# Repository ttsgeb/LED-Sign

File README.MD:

# LED Sign Board Revamp Project
This project aims to make the LED Sign Board a more valuable prototyping platform for learning usage of "neopixel" style LEDs  
It does this by developing the interface with the individual LED strips to enable easier wiring while also providing fusing for lengths of 64 LEDS  
Additionally it allows the 144/m strips to be spaced such that every two neopixels will make for one square pixel, which is satisfying despite halving the resolution when used.  

Parts list:
30m of 144/m WS2812 or compatible strip lights (~$400) 
2 * https://www.mcmaster.com/89015K189/  ~$100  
5/(2 Boards): https://www.digikey.com/en/products/detail/bourns-inc/MF-NSML400-12-2/9859205 ~$43 (60 total fuses)  
1/(2 Boards): https://www.digikey.com/en/products/detail/phoenix-contact/1017504/9346605 ~$12 (12 Connectors)  
Boards: https://www.pcbway.com/orderonline.aspx?outsideid=23cf7d91-80f4-4e14-90a0-6c2527d8c808 ~$55 (25 Boards)

Boards only total estimated cost: $110    Boards and backer total estimated cost: $210

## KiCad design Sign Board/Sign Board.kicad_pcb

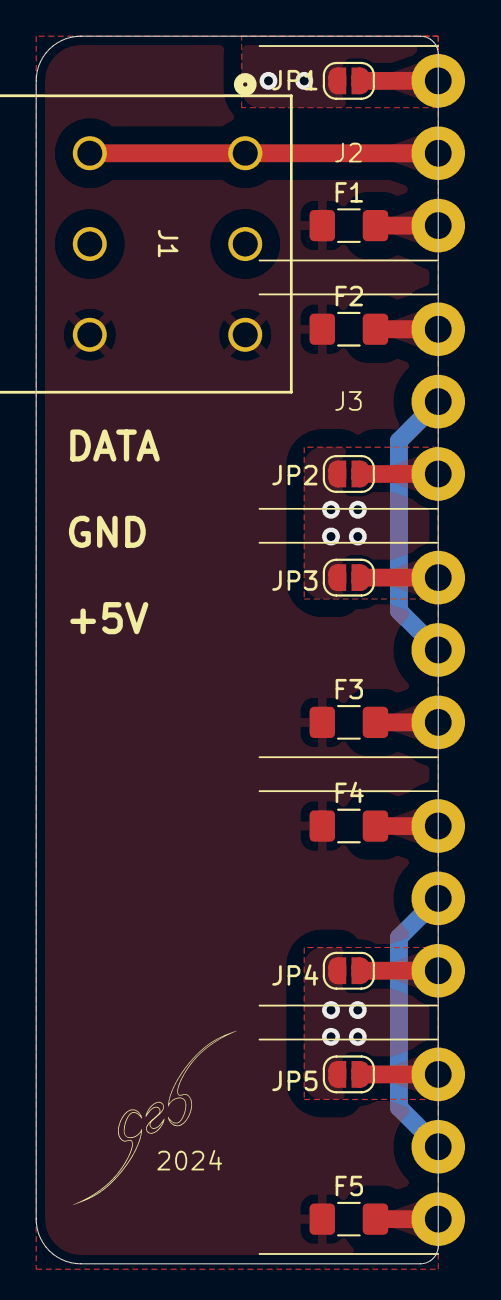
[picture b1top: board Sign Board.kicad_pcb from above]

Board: 2 copper layers, 22.5 x 68.7 mm, 17 parts (0 on the bottom side), 15 nets.

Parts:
2024: geblogo
F1, F2, F3, F4, F5: Polyfuse; Fuse_1206_3216Metric_Pad1.42x1.75mm_HandSolder
J1: Conn_01x03_Socket; CONN_1017492
J2, J3, J4, J5, J6: Conn_01x03_Pin; LED Strip Castlation
JP1, JP2, JP3, JP4, JP5: SolderJumper_2_Open; SolderJumper-2_P1.3mm_Open_RoundedPad1.0x1.5mm

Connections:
unnamed: F1.1, F2.1, F3.1, F4.1, F5.1, J1.5, J1.6
unnamed: F1.2, J2.1
unnamed: J2.2, JP1.2 (B)
unnamed: J1.1, J1.2, J2.3
unnamed: J3.1, JP2.2 (B)
unnamed: F2.2, J3.2
unnamed: J3.3, J4.3
unnamed: F3.2, J4.1
unnamed: J4.2, JP3.2 (B)
unnamed: J5.1, JP4.2 (B)
unnamed: F4.2, J5.2
unnamed: J5.3, J6.3
unnamed: F5.2, J6.1
unnamed: J6.2, JP5.2 (B)
unnamed: J1.3, J1.4, JP1.1 (A), JP2.1 (A), JP3.1 (A), JP4.1 (A), JP5.1 (A)

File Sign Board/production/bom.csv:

Designator,Footprint,Quantity,Value,LCSC Part #
"F1, F2, F3, F4, F5",1206,5,Polyfuse,
F6,Fuseholder_Blade_Mini_Keystone_3568,1,Fuse,
J1,TerminalBlock_Phoenix_MKDS-3-3-5.08_1x03_P5.08mm_Horizontal,1,Conn_01x03_Socket,
"J2, J3, J4, J5, J6",LED Strip Castlation,5,Conn_01x03_Pin,
"JP1, JP2, JP3, JP4, JP5",SolderJumper-2_P1.3mm_Open_RoundedPad1.0x1.5mm,5,SolderJumper_2_Open,

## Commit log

2024-04-02 Break Everything
2024-04-02 Magic
2024-04-02 Trying to fix my mistakes
2024-04-02 We'll get there eventually
2024-08-24 Reworked GND/Power planes and adjusted schematic to match application
